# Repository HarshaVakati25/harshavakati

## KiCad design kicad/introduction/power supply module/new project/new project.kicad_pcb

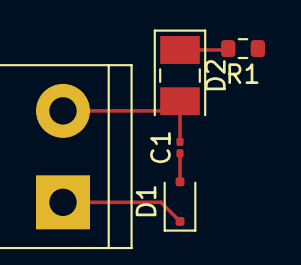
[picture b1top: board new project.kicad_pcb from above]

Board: 2 copper layers, 5 parts (0 on the bottom side), 4 nets.

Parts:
C1: C_Feedthrough; C_0201_0603Metric
D1: PMEG6002EJ; D_SOD-323F
D2: LED; LED_PLCC-2_3x2mm_AK
R1: R; R_0603_1608Metric
V1: 1; TerminalBlock_bornier-2_P5.08mm

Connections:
unnamed: C1.1, D1.2 (A)
unnamed: D1.1 (K), V1.1
unnamed: D2.2 (A), R1.2
unnamed: C1.2, D2.1 (K), V1.2

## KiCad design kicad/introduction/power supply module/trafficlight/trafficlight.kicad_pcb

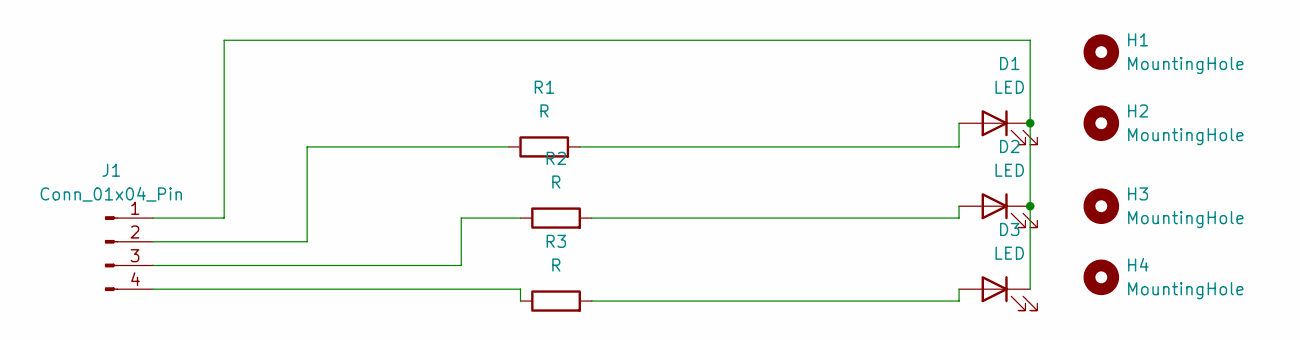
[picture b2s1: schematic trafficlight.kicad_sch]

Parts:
D1, D2, D3: LED; LED_D3.0mm
H1, H2, H3, H4: MountingHole; MountingHole_2.5mm_Pad
J1: Conn_01x04_Pin; PinHeader_1x04_P2.54mm_Horizontal
R1, R2, R3: R; R_Axial_DIN0204_L3.6mm_D1.6mm_P5.08mm_Horizontal

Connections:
unnamed: D1.2 (A), R1.2
unnamed: D1.1 (K), D2.1 (K), D3.1 (K), J1.1
unnamed: D2.2 (A), R2.2
unnamed: D3.2 (A), R3.2
unnamed: J1.2, R1.1
unnamed: J1.3, R2.1
unnamed: J1.4, R3.1

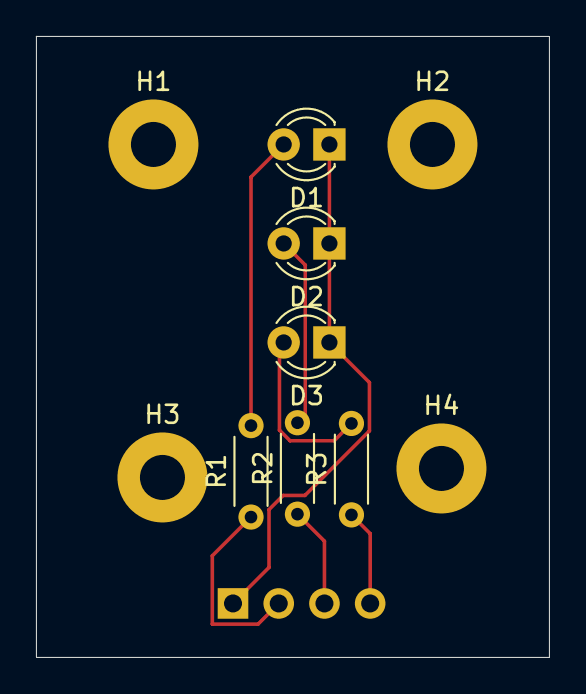
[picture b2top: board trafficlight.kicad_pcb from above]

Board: 2 copper layers, 28.5 x 34.5 mm, 11 parts (1 on the bottom side), 7 nets.

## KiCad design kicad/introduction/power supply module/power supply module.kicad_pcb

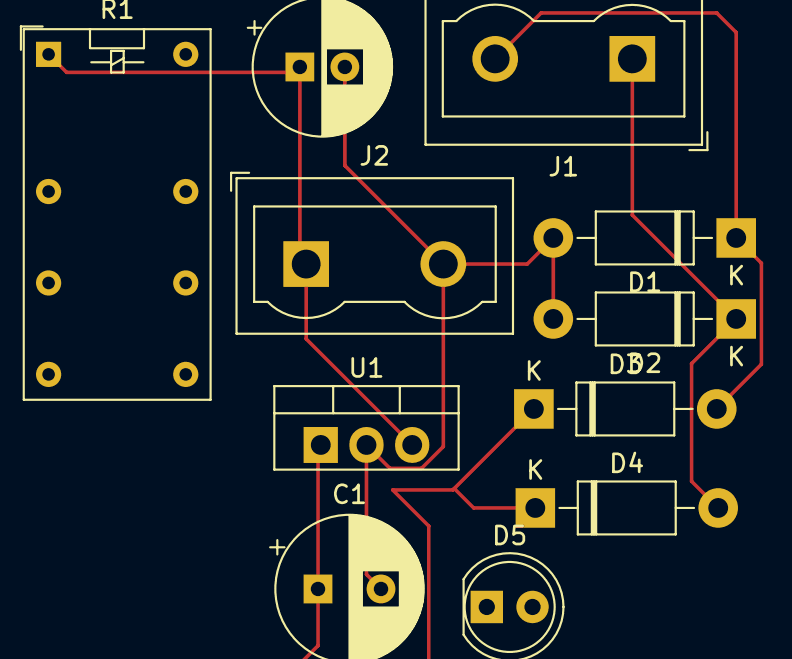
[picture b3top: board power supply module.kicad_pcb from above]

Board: 2 copper layers, 11 parts (0 on the bottom side), 5 nets.

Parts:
C1: 470 uf 25v; CP_Radial_D8.0mm_P3.50mm
C2: 100 uf; CP_Radial_D7.5mm_P2.50mm
D1, D2, D3, D4: 1N4007; D_DO-41_SOD81_P10.16mm_Horizontal
D5: LED; LED_D5.0mm
J1, J2: Screw_Terminal_01x02; TerminalBlock_Wuerth_691311400102_P7.62mm
R1: 1k; Relay_DPDT_Omron_G5V-2
U1: LM7805_TO220; TO-220-3_Vertical

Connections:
unnamed: C1.2, C2.2, D1.2 (A), D2.2 (A), D5.1 (K), J2.2, U1.2 (GND)
unnamed: D1.1 (K), D3.2 (A), J1.2
unnamed: D2.1 (K), D4.2 (A), J1.1
unnamed: C1.1, D3.1 (K), D4.1 (K), U1.1 (VI)
unnamed: C2.1, J2.1, R1.1, U1.3 (VO)

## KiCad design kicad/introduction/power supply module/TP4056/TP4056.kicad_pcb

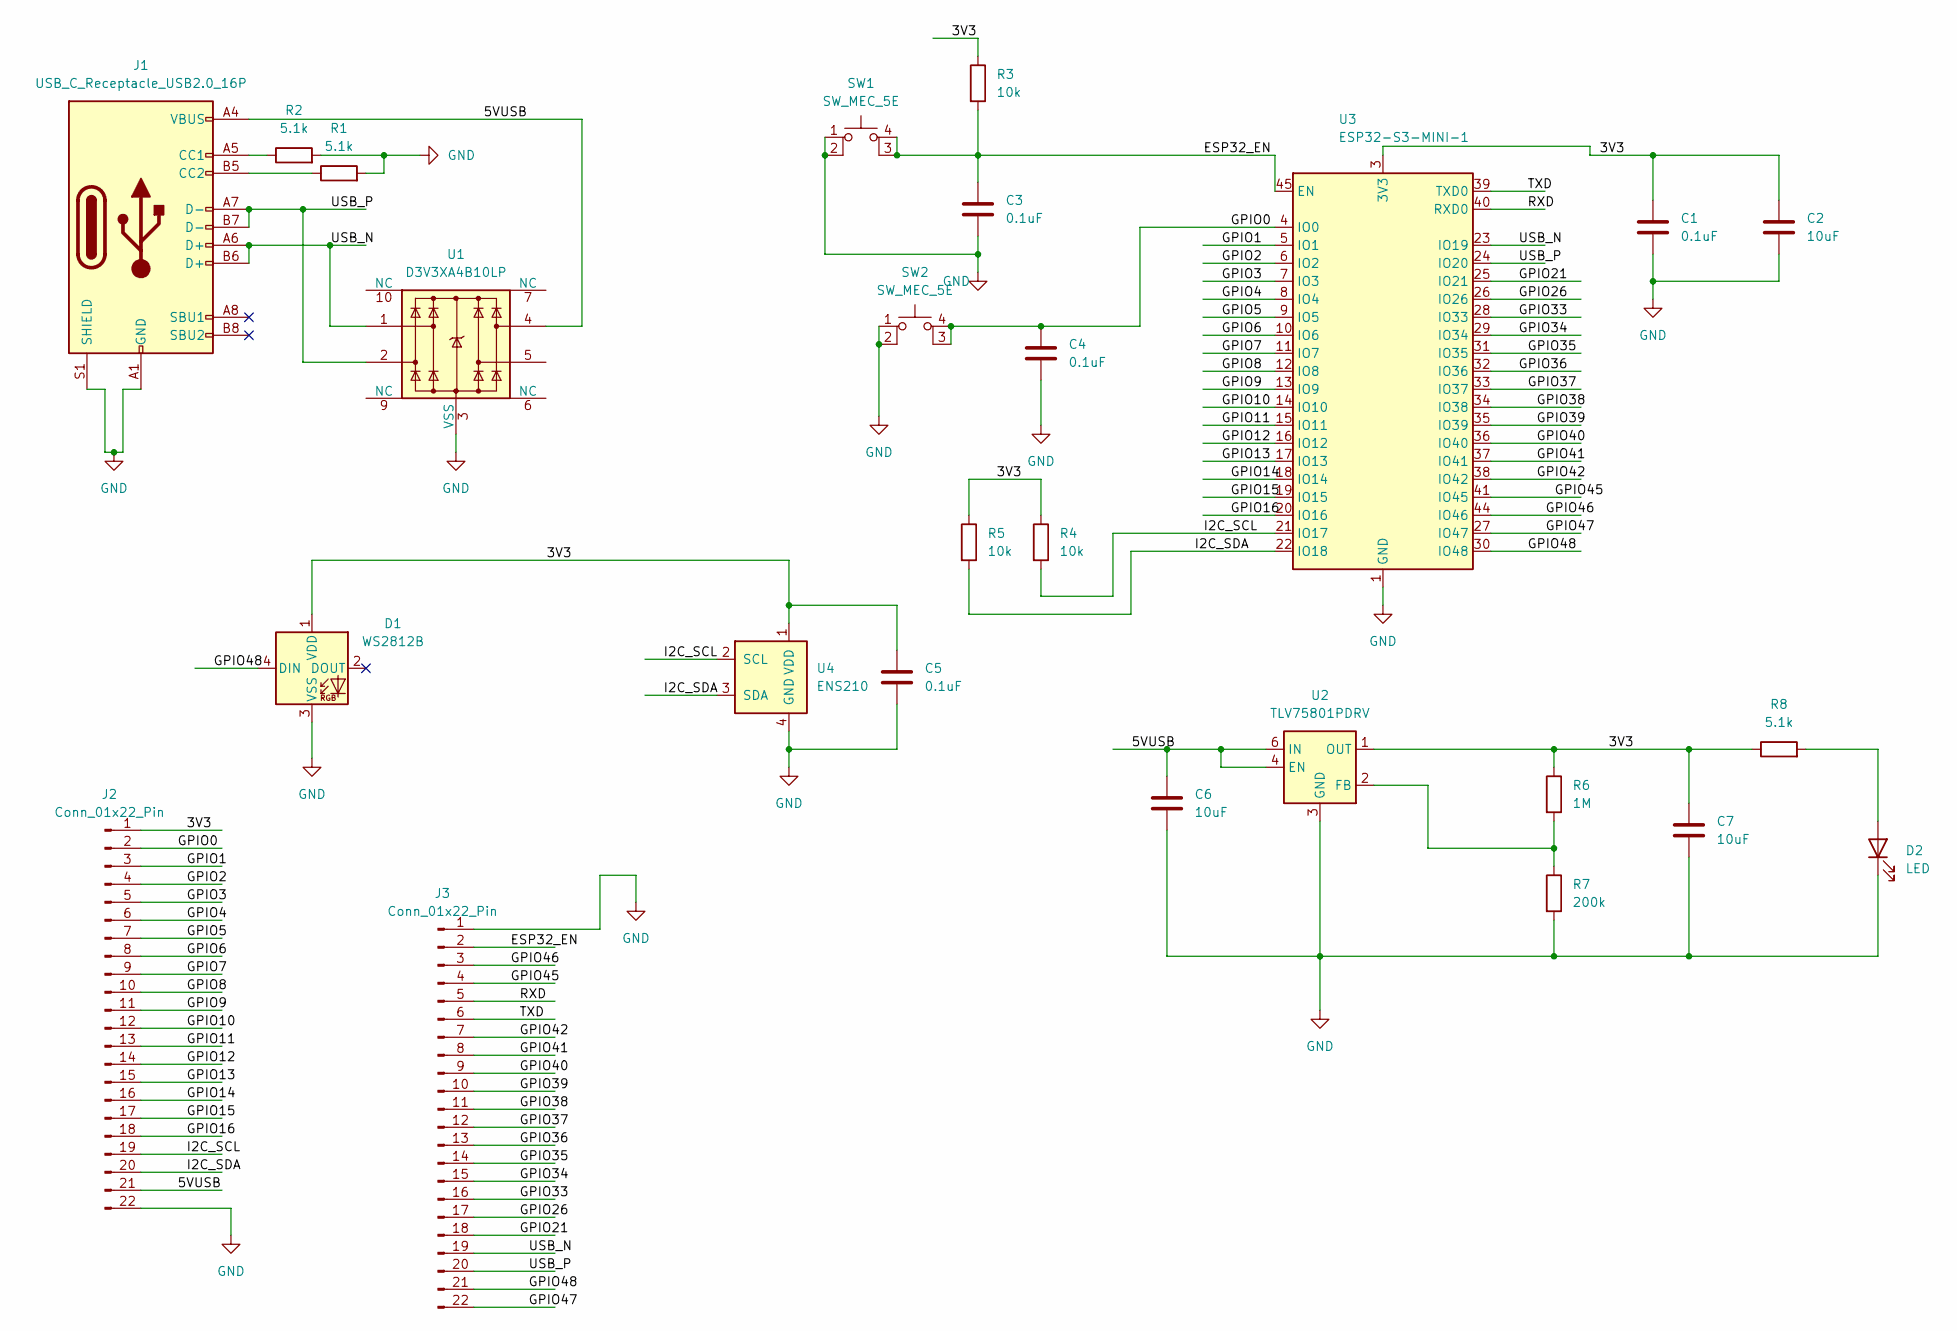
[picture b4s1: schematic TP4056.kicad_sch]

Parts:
C1, C3, C4, C5: 0.1uF; C_0603_1608Metric
C2, C6, C7: 10uF; C_0603_1608Metric
D1: WS2812B; LED_WS2812B_PLCC4_5.0x5.0mm_P3.2mm
D2: LED; LED_0603_1608Metric
J1: USB_C_Receptacle_USB2.0_16P; USB_C_Receptacle_GCT_USB4105-xx-A_16P_TopMnt_Horizontal
J2, J3: Conn_01x22_Pin; PinHeader_1x22_P2.54mm_Vertical
R1, R2, R8: 5.1k; R_0603_1608Metric
R3, R4, R5: 10k; R_0603_1608Metric
R6: 1M; R_0603_1608Metric
R7: 200k; R_0603_1608Metric
SW1, SW2: SW_MEC_5E; SW_SPST_PTS810
U1: D3V3XA4B10LP; Diodes_UDFN-10_1.0x2.5mm_P0.5mm
U2: TLV75801PDRV; WSON-6-1EP_2x2mm_P0.65mm_EP1x1.6mm
U3: ESP32-S3-MINI-1; ESP32-S2-MINI-1
U4: ENS210; AMS_QFN-4-1EP_2x2mm_P0.95mm_EP0.7x1.6mm

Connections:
/3V3: C1.1, C2.1, C5.1, C7.1, D1.1 (VDD), J2.1, R3.1, R4.1, R5.1, R6.1, R8.1, U2.1 (OUT), U3.3 (3V3), U4.1 (VDD)
/5VUSB: C6.1, J1.A4 (VBUS), J1.A9 (VBUS), J1.B4 (VBUS), J1.B9 (VBUS), J2.21, U1.4, U2.4 (EN), U2.6 (IN)
/ESP32_EN: C3.1, J3.2, R3.2, SW1.3 (K), SW1.4 (A), U3.45 (EN)
/GPIO0: C4.1, J2.2, SW2.3 (K), SW2.4 (A), U3.4 (IO0)
/GPIO1: J2.3, U3.5 (IO1)
/GPIO2: J2.4, U3.6 (IO2)
/GPIO3: J2.5, U3.7 (IO3)
/GPIO4: J2.6, U3.8 (IO4)
/GPIO5: J2.7, U3.9 (IO5)
/GPIO6: J2.8, U3.10 (IO6)
/GPIO7: J2.9, U3.11 (IO7)
/GPIO8: J2.10, U3.12 (IO8)
/GPIO9: J2.11, U3.13 (IO9)
/GPIO10: J2.12, U3.14 (IO10)
/GPIO11: J2.13, U3.15 (IO11)
/GPIO12: J2.14, U3.16 (IO12)
/GPIO13: J2.15, U3.17 (IO13)
/GPIO14: J2.16, U3.18 (IO14)
/GPIO15: J2.17, U3.19 (IO15)
/GPIO16: J2.18, U3.20 (IO16)
/GPIO21: J3.18, U3.25 (IO21)
/GPIO26: J3.17, U3.26 (IO26)
/GPIO33: J3.16, U3.28 (IO33)
/GPIO34: J3.15, U3.29 (IO34)
/GPIO35: J3.14, U3.31 (IO35)
/GPIO36: J3.13, U3.32 (IO36)
/GPIO37: J3.12, U3.33 (IO37)
/GPIO38: J3.11, U3.34 (IO38)
/GPIO39: J3.10, U3.35 (IO39)
/GPIO40: J3.9, U3.36 (IO40)
/GPIO41: J3.8, U3.37 (IO41)
/GPIO42: J3.7, U3.38 (IO42)
/GPIO45: J3.4, U3.41 (IO45)
/GPIO46: J3.3, U3.44 (IO46)
/GPIO47: J3.22, U3.27 (IO47)
/GPIO48: D1.4 (DIN), J3.21, U3.30 (IO48)
/I2C_SCL: J2.19, R4.2, U3.21 (IO17), U4.2 (SCL)
/I2C_SDA: J2.20, R5.2, U3.22 (IO18), U4.3 (SDA)
/RXD: J3.5, U3.40 (RXD0)
/TXD: J3.6, U3.39 (TXD0)
/USB_N: J1.A6 (D+), J1.B6 (D+), J3.19, U1.1, U3.23 (IO19)
/USB_P: J1.A7 (D-), J1.B7 (D-), J3.20, U1.2, U3.24 (IO20)
GND: C1.2, C2.2, C3.2, C4.2, C5.2, C6.2, C7.2, D1.3 (VSS), D2.1 (K), J1.A1 (GND), J1.A12 (GND), J1.B1 (GND), J1.B12 (GND), J1.S1 (SHIELD), J2.22, J3.1, R1.2, R2.2, R7.2, SW1.1, SW1.2, SW2.1, SW2.2, U1.3 (VSS), U1.8 (VSS), U2.3 (GND), U2.7 (GND), U3.1 (GND), U3.2 (GND), U3.42 (GND), U3.43 (GND), U3.46 (GND), U3.47 (GND), U3.48 (GND), U3.49 (GND), U3.50 (GND), U3.51 (GND), U3.52 (GND), U3.53 (GND), U3.54 (GND), U3.55 (GND), U3.56 (GND), U3.57 (GND), U3.58 (GND), U3.59 (GND), U3.60 (GND), U3.61 (GND), U3.62 (GND), U3.63 (GND), U3.64 (GND), U3.65 (GND), U4.4 (GND), U4.5 (GND)
unnamed: D2.2 (A), R8.2
unnamed: J1.A5 (CC1), R2.1
unnamed: J1.B5 (CC2), R1.1
unnamed: R6.2, R7.1, U2.2 (FB)

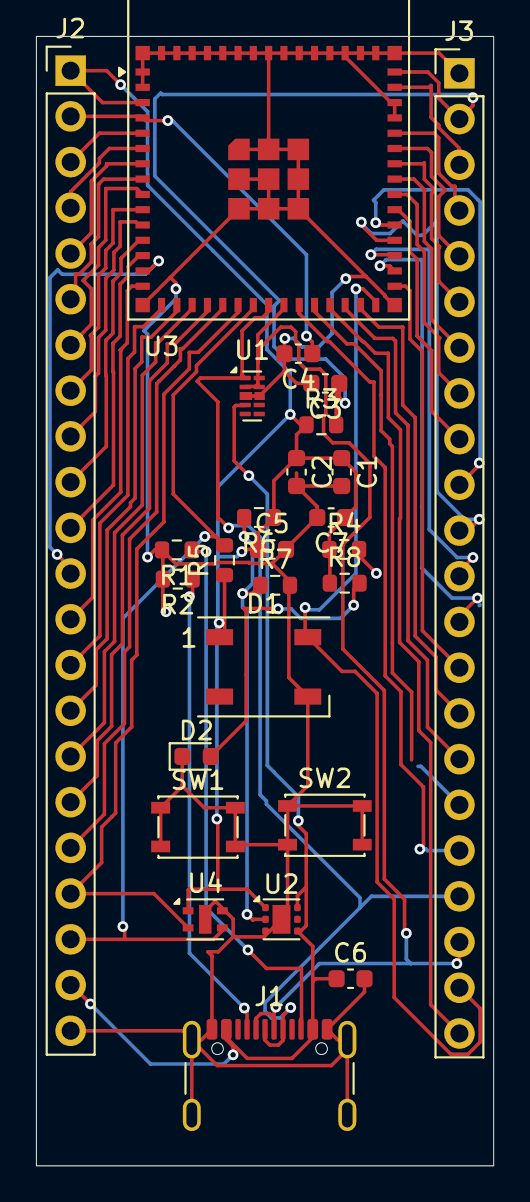
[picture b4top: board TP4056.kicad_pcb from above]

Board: 2 copper layers, 25.4 x 62.7 mm, 26 parts (0 on the bottom side), 47 nets.
